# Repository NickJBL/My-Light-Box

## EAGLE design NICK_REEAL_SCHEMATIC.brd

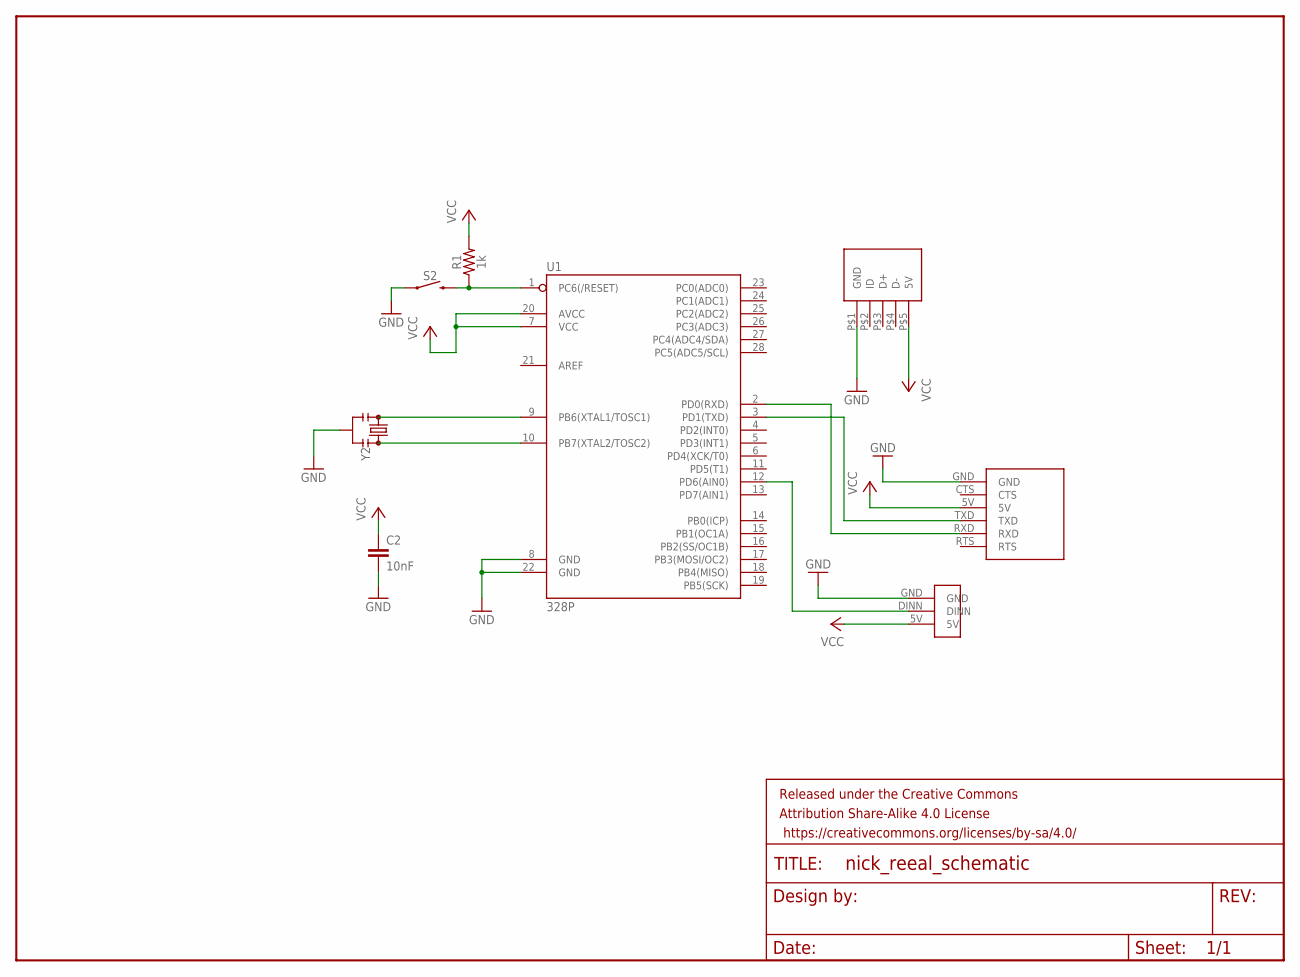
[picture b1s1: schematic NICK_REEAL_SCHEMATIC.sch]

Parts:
C2: 10nF; CAP-PTH-10MM
FRAME1: FRAME-LETTERNO_PACKAGE; DUMMY
R1: 1k; AXIAL-0.3
S2: MOMENTARY-SWITCH-SPST-PTH-6.0MM; TACTILE_SWITCH_PTH_6.0MM
U1: 328P; DIP28
U$1: USBCONNECTER
U$2: PROGRAMCABLE
U$3: 8LEDCONNECTER
Y2: RESONATORPTH-7.6X3.8; RESONATOR-PTH-7.6X3.8

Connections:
GND: C2.2, S2.1, U1.8 (GND), U1.22 (GND), U$1.P$1 (GND), U$2.GND, U$3.GND, Y2.2
unnamed: U1.9 (PB6(XTAL1/TOSC1)), Y2.3
unnamed: U1.10 (PB7(XTAL2/TOSC2)), Y2.1
unnamed: U1.3 (PD1(TXD)), U$2.TXD
unnamed: R1.P$1 (1), S2.3 (2), U1.1 (PC6(/RESET))
unnamed: U1.2 (PD0(RXD)), U$2.RXD
unnamed: U1.12 (PD6(AIN0)), U$3.DINN
VCC: C2.1, R1.P$2 (2), U1.7 (VCC), U1.20 (AVCC), U$1.P$5 (5V), U$2.5V, U$3.5V

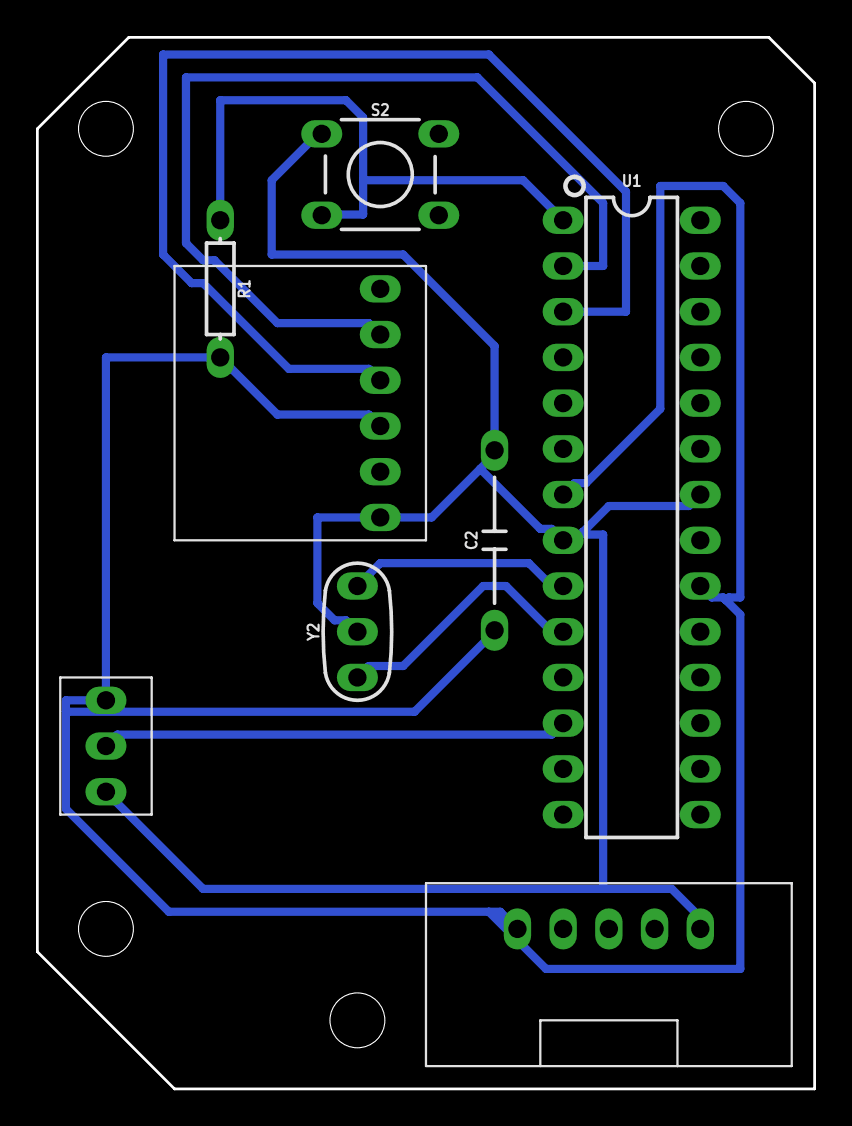
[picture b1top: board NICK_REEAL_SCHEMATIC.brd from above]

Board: 2 copper layers, 43.2 x 58.4 mm, 9 parts (0 on the bottom side), 8 nets.

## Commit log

2019-01-30 1st commit
2019-02-14 Create Robotics Price Sheet.xlsx
    Added my Light Box price sheet
2019-02-14 Create simple.ino
    Code for Light Box
2019-02-14 Revert "Create simple.ino"
    This reverts commit ba55fe046034ec5745f11087eedae77cba887811.
2019-02-14 Revert "Revert "Create simple.ino""
    This reverts commit cbcea7450b8fdc17c59a29eab1f8026cc7ac2b83.
2019-02-14 Create Light_Box_Code.ino
    Arduino Light Box Code

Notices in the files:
parts and their libraries:
SparkFun-Aesthetics: Licensing: Creative Commons ShareAlike 4.0 International - https://creativecommons.org/licenses/by-sa/4.0
SparkFun-Aesthetics: Released under the Creative Commons Attribution Share-Alike 4.0 License
SparkFun-Aesthetics: https://creativecommons.org/licenses/by-sa/4.0
